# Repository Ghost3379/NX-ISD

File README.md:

# NX-ISD

## Overview
The **NX-ISD** is a custom, highly integrated wearable and embedded development board inspired by the Artemis Watch. It serves as the hardware foundation for the **ISD-Core** operating system.

> [!TIP]
> **Active Production Milestone — Hardware Revision v1.4 (Current & Recommended):**  
> Revision **v1.4** is the active, production-ready hardware milestone featuring an integrated rechargeable supercapacitor for continuous RTC timekeeping, high-speed 4-bit SDMMC MicroSD storage, a direct 40 MHz 3.3V SPI display bus (TXB0106 level shifter eliminated), tactile BOOT/RST buttons, enhanced copper heatsinking, and a cyberpunk industrial silkscreen aesthetic.  
> 📦 **Fabrication Package (Gerbers & Drill):** [`ISD-PCB/NX-ISD_v1p4/production/NX-ISD_v1p4.zip`](ISD-PCB/NX-ISD_v1p4/production/NX-ISD_v1p4.zip)  
> 📜 **Complete 5-Page Circuit Diagram:** [`docs/circuit diagrams/NX-ISD_v1p4.pdf`](docs/circuit%20diagrams/NX-ISD_v1p4.pdf)  
> 🏭 **Fabrication & Ordering Guide:** [`ISD-PCB/PRODUCTION-GUIDE.md`](ISD-PCB/PRODUCTION-GUIDE.md)

<p align="center">
  <em>NX-ISD Hardware Revision v1p4 (KiCad Raytraced 3D Renders) — Populated Top View, Bottom Silkscreen, Perspective Isometric Angle, and Bare ENIG Finish.</em>
</p>

## Naming & Structure

```text
N X - I S D
│     │
│     └─► Intelligent Sensor Device (Hardware Foundation)
│           │
│           ▼
│       ISD-Core
│           │
│           ├─► Custom Operating System (Dual-Core FreeRTOS based)
│           ├─► Built on PlatformIO / Arduino Framework
│           │
│           ├──► NX-MSF: Mathematical Sensor Fusion (Physics Models & Kalman Filters)
│           ├──► NX-AIS: Advanced Information System (Contextual Advisory Engine)
│           └──► NX-SDS: Self-Diagnostic System (Hardware Integrity & Proof-Testing)
│
└─► Prototyping Series (Continuous Development Environment)
```

* **Hardware Lineage:** Originally inspired by and iterated from the [Artemis Watch](https://circuitmess.com/products/nasa-artemis-watch) (and subsequently the [Artemis Watch 2.0](https://circuitmess.com/products/nasa-artemis-watch-2-0)) by CircuitMess, heavily expanded into a custom tactical multi-sensor wearable.
* **The "NX" Philosophy:** Inspired by Starfleet's experimental registry designation ([Memory Alpha: NX](https://memory-alpha.fandom.com/wiki/NX)), the **NX** prefix denotes an active, pioneering prototyping environment. Rather than static consumer electronics, each build is a working experimental platform. Once a revision is tagged and published, that milestone is locked in history—quirks, bugs, and all:
  * **Revision v1.4 (Current & Recommended):** Production revision with MicroSD (4-bit SDMMC), supercapacitor RTC backup, direct 40 MHz SPI display bus, and physical RST/BOOT buttons. [`ISD-PCB/NX-ISD_v1p4/`](ISD-PCB/NX-ISD_v1p4/)
  * **Revision v1.3 (Prototype Carrier):** First operational wearable prototype assembly with NAND flash and TXB0106 display shifter. [`ISD-PCB/NX-ISD_v1p3/`](ISD-PCB/NX-ISD_v1p3/)
  * **Revision v1.0 (Initial Prototype Archive):** The original, raw starting schematics, early layout, and BOM preserved for historical nostalgia, open-source transparency, and post-mortem analysis. [`ISD-PCB/NX-ISD_v1p0/`](ISD-PCB/NX-ISD_v1p0/)

## Hardware Specifications (Revision v1.4)

### Core & Storage
* **Microcontroller:** ESP32-S3-WROOM-1-N16R8 (Dual-Core Xtensa LX7 @ 240MHz, 16MB Quad-SPI Flash, 8MB Octal PSRAM)
* **High-Speed Mass Storage:** MicroSD Card Slot (`J4`, Molex 105162-0001) operating in 4-bit SDMMC bus mode via the ESP32-S3 GPIO Matrix (`SD_CLK` IO41, `SD_CMD` IO43, `SD_DAT0` IO44, `SD_DAT1` IO42, `SD_DAT2` IO1, `SD_DAT3` IO2)

### Sensors & Biometrics
* **Motion / 9-DOF IMU:** BNO085 (CEVA / Hillcrest Labs AR/VR Motion Co-Processor with dedicated 32.768 kHz crystal `Y1`)
* **Environment:** BME680 / BME690 (Bosch Sensortec Gas MOX, Barometric Pressure, Relative Humidity, Temperature)
* **Ambient Light:** OPT3001DNPR (Texas Instruments Precision Photopic Lux Sensor)
* **Biometrics / PPG:** MAX30102 (Pulse Oximetry $SpO_2$ & Heart-Rate Biosensor, isolated on 1.8V domain via PCA9306DCKR bidirectional level shifter `U9`)
* **Precision Timing & RTC:** RV-3028-C7 (Micro Crystal Switzerland, 45 nA typ.) backed by an integrated **11 mF 3.3V Seiko `CPH3225A` rechargeable supercapacitor (`C5`)** charged via internal silicon trickle charger (~6.2 days continuous autonomous timekeeping)

### Power Management & Thermal Design
* **Battery Charging:** USB-C (BQ25170 Linear LiPo Charger configured for 600mA charging into 1S 1200mAh LiPo; enhanced bottom GND thermal relief plating)
* **Fuel Gauge:** MAX17048G_T10 (ModelGauge™ cell voltage tracking, state-of-charge %, and `!ALERT` interrupt line)
* **System Rail (+3V3):** TLV62568 Synchronous Step-Down Buck Converter (1A rating, ~95% efficiency, 2.2µH power inductor)
* **Sensor Rail (+1V8):** RT9193-18GB Ultra-Low-Noise LDO (300mA rating, dedicated clean analog rail for MAX30102 core)
* **Power-Path & Switches:** High-efficiency `DMP3130L-7` P-MOSFETs for USB/Battery power-path management and NeoPixel sleep cutoff; `ZXMN3B14FTA` 30V N-MOSFETs for acoustic buzzer and display backlight control

### Peripherals & User Interaction
* **Display Interface:** [1.54" 240×240 IPS Color TFT (ST7789V2)](https://de.aliexpress.com/item/1005007654038756.html) connected via 10-pin 0.5mm dual-contact FPC connector (`J3`). Operates natively on a **direct 3.3V SPI bus at 40 MHz** (TXB0106 level shifter eliminated for rock-solid signal integrity)
* **Optical Matrix:** 16x NeoPixel 4×4 Serpentine RGB Matrix (XL-1010RGBC-WS2812B) with zero-leakage PMOS high-side power gate (`IO17` enable, `IO18` data) and local decoupling capacitors
* **Acoustic Transducer:** 16Ω Electromagnetic SMT Buzzer (`SMD-8503-3627-16Ω`) with flyback diode protection
* **Input Controls:**
  * Multi-Directional Navigation Lever-Switch (`TM-2025A` 5-way navigation: Up, Down, Left, Right, Center Push)
  * Main Tactical User Push-Button with hardware pull-up for deep-sleep wake
  * Dedicated Tactile **BOOT** (`SW2`) and **RST** (`SW1`) Micro Push-Buttons for effortless flashing and recovery

## Software & Core Systems
The board is programmed via **PlatformIO** (Arduino Framework) and is optimized to run the custom **ISD-Core** operating system. The software stack is composed of core modular subsystems:

* **[ISD-Core](ISD-Core/):** The dual-core FreeRTOS operating system handling task scheduling (Core 1 UI @ ~42Hz, Core 0 Sensors @ 50Hz/1Hz), thread-safe `SensorState` telemetry, 3D Cover Flow launcher, 360° radial dials, and smoothstep backlight transitions. See [`ISD-Core/README.md`](ISD-Core/README.md) for the software architecture and [`ISD-Core/MANUAL.md`](ISD-Core/MANUAL.md) for the complete user manual.
* **Persistent Storage Subsystem (`StorageManager`):** Manages non-volatile configuration storage, sensor logs, and system data on high-speed MicroSD storage (`4-bit SDMMC` mode on v1.4 hardware; SPI NAND on legacy v1.3 prototype). Stores a 64-byte packed binary struct (`/sys/config.bin`) with CRC-16 validation and a zero-wear save policy (writes occur only on user confirmation/exit, never while dialing).
* **Unified Host CLI & Config Engine (`tools/isd_cli.py` / `isd-cli`):** Standalone PC terminal tool providing blind navigation control, live sensor monitoring, BLE Uplink Bridge triggering, and offline `/sys/config.bin` binary inspection, verification, and JSON conversion.
* **NX-MSF (Mathematical Sensor Fusion):** The analytical physics and math engine executing 1D Kalman filter variometer tracking, Magnus-Tetens dew point calculation, barometric storm gradients, RMSSD heart rate variability, and software energy accounting.
* **NX-AIS (Advanced Information System):** The autonomous on-device contextual advisor translating raw multi-sensor telemetry into proactive health, environmental, and tactical notifications.
* **NX-SDS (Self-Diagnostic System):** The internal hardware integrity and health assurance engine providing continuous I2C bus recovery, on-demand in-situ proof-testing, and predictive battery/sensor aging analytics.

## Documentation & Manuals
* **Hardware Production & Fabrication Guide:** [`ISD-PCB/PRODUCTION-GUIDE.md`](ISD-PCB/PRODUCTION-GUIDE.md) — Complete JLCPCB ordering parameters, mechanical drawings/dimensions, stencil specs, and hand assembly workflow.
* **Fabrication Packages (Gerbers):** [`ISD-PCB/NX-ISD_v1p4/production/NX-ISD_v1p4.zip`](ISD-PCB/NX-ISD_v1p4/production/NX-ISD_v1p4.zip) — Ready-to-order RS-274X Gerbers and drill files for revision v1.4.
* **Interactive HTML BOM (Visual Assembly Tool):** [`ISD-PCB/NX-ISD_v1p4/bom/NX-ISD_v1p4_IBOM.html`](ISD-PCB/NX-ISD_v1p4/bom/NX-ISD_v1p4_IBOM.html) — Interactive visual assembly BOM highlighting components and pads.
* **User & Navigation Manual:** [`ISD-Core/MANUAL.md`](ISD-Core/MANUAL.md) — Comprehensive guide covering physical controls, screen layouts, the 6 core application decks, 360° radial dials, and storage persistence.
* **Architecture & Hardware Guide:** [`ISD-Core/README.md`](ISD-Core/README.md) — Technical operating system internals, pin maps, and PlatformIO build instructions.
* **Hardware & PCB Specifications:** [`ISD-PCB/README.md`](ISD-PCB/README.md) — Hardware schematics, power budgets, layer stackup, and BOM.
* **Features & Math Modeling Roadmap:** [`FEATURE_LIST.md`](FEATURE_LIST.md) — Technical specifications, mathematical formulas, and implementation roadmap.
* **Software Roadmap & TODOs:** [`ISD-Core/SW-TODO.md`](ISD-Core/SW-TODO.md) — Core application deck progress and feature checklist.

## AI Collaboration & Transparency Disclaimer
In the spirit of full open-source transparency:
* **AI Assistance:** Generative AI pair-programming tools were used to assist with documentation drafting, software architecture refinement, mathematical formula translations, and repository organization.
* **Engineering & Ownership:** All hardware schematics, PCB routing, component selection, electrical calculations, physical assembly, and system verification remain 100% human-engineered, tested, and maintained by the author ([@Ghost3379](https://github.com/Ghost3379)).

## License
The software/firmware in the [ISD-Core] directory is licensed under the GNU General Public License v3.0 (GPLv3).

The hardware design files in the [ISD-PCB] directory are licensed under the CERN Open Hardware Licence Version 2 - Strongly Reciprocal (CERN-OHL-S).

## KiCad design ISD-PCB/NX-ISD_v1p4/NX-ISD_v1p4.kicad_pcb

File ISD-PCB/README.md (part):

# NX-ISD Hardware Specification (Revision v1p4 - Current & Recommended)

This directory contains the schematic design, PCB layout, fabrication outputs, and Bill of Materials (BOM) for the **NX-ISD** (Intelligent Sensor Device) wearable carrier board.

<p align="center">
  <em>NX-ISD Hardware Revision v1p4 (KiCad Raytraced 3D Renders) — Populated Top View, Bottom Silkscreen, Perspective Isometric Angle, and Bare ENIG Finish with "PUT THAT BACK!" Silkscreen Easter Egg</em>
</p>

> [!TIP]
> **Production & Ordering Guide (v1.4):** For complete mechanical drawings, JLCPCB ordering parameters, SMD stencil specs, and hand assembly tips, see the **[Production Guide](PRODUCTION-GUIDE.md)**.  
> 📦 **Latest v1.4 Fabrication Package:** [`NX-ISD_v1p4/production/NX-ISD_v1p4.zip`](NX-ISD_v1p4/production/NX-ISD_v1p4.zip) (Ready for JLCPCB / PCBWay).  
> 📜 **Latest v1.4 Circuit Diagram (5 Sheets):** [`../docs/circuit diagrams/NX-ISD_v1p4.pdf`](../docs/circuit%20diagrams/NX-ISD_v1p4.pdf).

---

## 1. Board Specifications & Physical Dimensions

| Parameter | Specification | Notes |
| :--- | :--- | :--- |
| **Dimensions** | **77.00 mm × 48.60 mm** | Measured outer bounding box on `Edge.Cuts` |
| **Board Thickness** | **1.2 mm** | Standard FR-4 rigid substrate (optimal wrist comfort & rigidity) |
| **Layer Count** | **4 Layers** | Optimized signal integrity, unbroken GND plane, and dedicated power pours |
| **Copper Weight** | 1 oz Outer (35 µm), 1 oz Inner | Standard manufacturing yield with thermal relief |
| **Surface Finish** | ENIG (Electroless Nickel Immersion Gold) | Mandatory for fine-pitch QFN/WSON sensors and 0402 passives |
| **Strap Mounts** | Dual integrated strap slots | Accommodates standard 20 mm – 28 mm watch straps |
| **Antenna Clearance** | Dedicated bottom keep-out zone | `RF-AREA KEEP FREE` silkscreen below ESP32-S3 PCB antenna |
| **Primary Connector** | 16-Pin Mid-Mount USB Type-C | USB 2.0 Full Speed + 5V 600mA charging |
| **Battery Header** | JST PH 2.0mm 2-Pin (`J2`) | Polarized 1S LiPo (1200 mAh form factor) |
| **Mass Storage** | Push-Pull MicroSD Socket (`J4`) | High-speed 4-bit SDMMC bus interface |

### 4-Layer PCB Stackup

```text
┌────────────────────────────────────────────────────────────────────────┐
│ Layer 1: Top (F.Cu)       High-density signal routing, IC pads, GND    │
├────────────────────────────────────────────────────────────────────────┤
│ Layer 2: Inner 1 (In1.Cu) Solid uninterrupted Ground Plane (GND)       │
├────────────────────────────────────────────────────────────────────────┤
│ Layer 3: Inner 2 (In2.Cu) Power Planes (+3V3, VBAT, +1V8, VN)          │
├────────────────────────────────────────────────────────────────────────┤
│ Layer 4: Bottom (B.Cu)    Secondary routing, thermal pads, silkscreen  │
└────────────────────────────────────────────────────────────────────────┘
```

---

## 2. Power Architecture & Voltage Domains (v1.4)

```text
               ┌───────────────────────┐
  USB-C (5V) ─►│ BQ25170 Charger (U3)  ├──► VBAT (3.7V - 4.2V, 1S LiPo via J2)
               │ (600mA, 10k NTC TH1)  │         │
               └───────────────────────┘         ├─► MAX17048 Fuel Gauge (U6)
                                                 │
  ┌──────────────────────────────────────────────┘
  │
  ├──► TLV62568 Buck Converter (U4) ──► +3V3 (System Rail, ~95% Efficiency)
  │    (2.2µH L1, 10µF filtering)         │
  │                                       ├─► ESP32-S3 Microcontroller (U2)
  │                                       ├─► BNO085 9-DOF IMU (U11)
  │                                       ├─► BME690 Environmental (U7)
  │                                       ├─► OPT3001 Ambient Light (U10)
  │                                       ├─► RV-3028-C7 RTC (U12)
  │                                       ├─► MicroSD Card Slot (J4)
  │                                       ├─► ST7789 IPS Display Logic & Backlight (J3 / Q4)
  │                                       └─► Buzzer LS1 (via Q3)
  │
  ├──► RT9193-18GB LDO (U5) ──────────► +1V8 (Ultra-Low-Noise Sensor Rail)
  │    (Ultra-Low Noise, 300mA)           ├─► MAX30102 PPG / Biometrics (U8)
  │                                       └─► PCA9306 I2C Level Shifter (U9, Port 1)
  │
  ├──► DMP3130L-7 PMOS Gate (Q1) ──────► VN   (Switched VBAT Rail, 3.0V - 4.2V)
  │    (Driven by IO17 via BC847W)        └─► 16x NeoPixel Matrix (G1..G16)
  │                                           [Guarantees 0µA sleep draw]
  │
  └──► RV-3028-C7 Internal Charger ───► VBACKUP (Autonomous Supercapacitor Rail)
       (Switch + Schottky + 3k Ladder)    └─► 11mF 3.3V Seiko CPH3225A (C5)
                                              [~6.2 Days RTC timekeeping backup]
```

### Voltage Rail Details

| Rail | Nominal Voltage | Regulator / Source | Max Current | Consumers |
| :--- | :--- | :--- | :--- | :--- |
| **`VBUS`** | 5.0 V (4.75–5.25V) | USB Type-C Receptacle (`J1`) | 1.5 A | BQ25170 Charger, USB detect divider, USBLC6 ESD |
| **`VBAT`** | 3.7 V (3.0–4.2V) | 1S LiPo via JST PH (`J2`) | 2.0 A peak | Buck converter, LDO, Fuel Gauge, VN PMOS switch, Power-Path PMOS (`Q2`) |
| **`+3V3`** | 3.3 V (±1.5%) | TLV62568DBVR Synchronous Buck (`U4`)| 1.0 A | ESP32-S3, BNO085, BME690, OPT3001, RV-3028, MicroSD, ST7789 Display, Buzzer |
| **`+1V8`** | 1.8 V (±2.0%) | RT9193-18GB Low-Noise LDO (`U5`) | 300 mA | MAX30102 logic core, PCA9306 level shifter low-side |
| **`VN`** | Switched `VBAT` | DMP3130L-7 High-Side PMOS (`Q1`) | 1.0 A | 16x XL-1010RGBC NeoPixels (0µA cutoff when unpowered) |
| **`VBACKUP`**| 3.3 V max (1.1–3.05V)| RV-3028-C7 Internal Trickle Charger| 1.0 mA chg | Pin 6 of RV-3028-C7 backed by $11\text{ mF}$ CPH3225A Supercap (`C5`) |

---

## 3. Power Consumption Budget & Battery Calculation

Comprehensive current consumption analysis across operating states, accounting for conversion efficiencies and real-world loads:

### 1. Subsystem Current Breakdown

#### A. 16× NeoPixel RGB Matrix (`G1`–`G16`, on Switched `VN` / `VBAT`)
* **Driver Constant-Current Sink:** $5.0\,\text{mA}$ per color channel (R, G, B).
* **Per LED at 100% White:** $(3 \times 5.0\,\text{mA}) + 0.35\,\text{mA}$ (internal logic) $\approx \mathbf{15.35\,\text{mA}}$.
* **100% White Matrix Stress Test (16 LEDs):** $16 \times 15.35\,\text{mA} \approx \mathbf{245.6\,\text{mA}}$ (drawn directly from `VBAT` through PMOS `Q2`).
* **Dynamic Cyberpunk Animations (`CYBER RADAR`, `NEON TRACER`, etc.):** 2 to 5 active LEDs at 30–60% intensity $\approx \mathbf{15\text{ to }35\,\text{mA}}$ average.
* **Standby / Off State (`PWR_NPM` = LOW):** High-side PMOS `Q2` is gated off by pull-up $\implies \mathbf{0.00\,\mu\text{A}}$ (completely eliminates NeoPixel quiescent leakage).

#### B. ESP32-S3 Dual-Core Microcontroller (`U13`, on `+3V3`)
* **Active Wi-Fi TX (Max power + Dual-Core processing):** $\approx 240\text{ to }350\,\text{mA}$ (transient peaks up to $\approx 450\,\text{mA}$).
* **Active BLE Connected / Advertising:** $\approx 35\text{ to }55\,\text{mA}$.
* **Normal Dual-Core Processing (No RF, 240 MHz):** $\approx 40\text{ to }65\,\text{mA}$.
* **Frequency-Scaled Run (80 MHz / 160 MHz):** $\approx 20\text{ to }35\,\text{mA}$.
* **FreeRTOS Light-Sleep (Between 50Hz/1Hz sensor ticks):** $\approx 1.5\text{ to }3.0\,\text{mA}$.
* **Deep-Sleep (ULP / RTC wake only):** $\approx 15\text{ to }25\,\mu\text{A}$.

#### C. ST7789 IPS Display (`J2`, on `+3V3` & `+2V8`)
* **Backlight LEDs (via `+3V3` switched by N-MOSFET `Q4`):**
  * 100% Brightness: $\approx 35\text{ to }45\,\text{mA}$.
  * 40% Indoor Brightness: $\approx 15\text{ to }20\,\text{mA}$.
* **Display Controller Logic (via `+2V8` LDO `U4`):** $\approx 5\text{ to }10\,\text{mA}$.
* **Display Sleep Mode (`SLPIN` command):** $< 20\,\mu\text{A}$.
* **Total Display Active:** $\approx 20\text{ to }55\,\text{mA}$.

#### D. Sensors, Audio & Storage Peripherals
* **MAX30102 Biometrics (`U8`, on `+1V8` LDO `U1`):**
  * Time-averaged optical pulse current (Red + IR LEDs @ 50–100 Hz): $\approx 10\text{ to }18\,\text{mA}$ (peaks of $50\,\text{mA}$ during $400\,\mu\text{s}$ pulses).
  * Standby / Shutdown: $< 1\,\mu\text{A}$.
* **BNO085 9-DOF IMU (`U11`, on `+3V3`):**
  * Active 9-axis sensor fusion (internal ARM Cortex-M0+ running at 100 Hz): $\approx 15\text{ to }18\,\text{mA}$.
  * Low-power tap / step-detector only: $\approx 0.8\text{ to }1.5\,\text{mA}$.
* **BME690 Environmental (`U7`, on `+3V3`):**
  * Base climate sampling (T/P/H): $< 1\,\text{mA}$.
  * MOX Gas Heater Pulse (heats to $320^\circ\text{C}$ for $\approx 30\,\text{ms}$): $\mathbf{+12\text{ to }14\,\text{mA}}$ transient burst.
* **B1 Electromagnetic Buzzer (`B1`, on `+3V3` via `Q3`):**
  * $16\,\Omega$ coil impedance at $3.3\,\text{V}$: Peak current $\approx 206\,\text{mA}$.
  * 50% PWM Duty Cycle acoustic tone: $\approx \mathbf{80\text{ to }100\,\text{mA}}$ average (only when sounding alert/alarm).
* **ZDSD02GLGEAG SPI NAND Flash (`U14`, on `+3V3`):**
  * Standby: $\approx 10\,\mu\text{A}$.
  * High-speed SPI Read/Write bursts: $\approx 15\text{ to }25\,\text{mA}$.
* **OPT3001 Ambient Light (`U10`, on `+3V3`):** $\approx 2\text{ to }4\,\mu\text{A}$ (quiescent).
* **RV-3028-C7 RTC (`U12`, on `+3V3`):** $\approx 45\,\text{nA}$ (running continuously).
* **LDO Quiescent Currents (`U1`, `U4`):** $\approx 90\,\mu\text{A}$ each.

---

### 2. Supply Rail Power Budget & Buck Efficiency

#### `+3V3` System Rail (TLV62568 Synchronous Buck `U3`):
* **Normal Operation (Display on, sensors active, Wi-Fi off):** $\approx 80\text{ to }130\,\text{mA}$.
* **Full Load (Wi-Fi TX active, display 100%, all sensors active, BME690 heater):** $\approx \mathbf{320\text{ to }460\,\text{mA}}$.
* **Absolute Worst-Case Transient (+ Buzzer beeping):** $\approx 550\text{ to }640\,\text{mA}$.
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
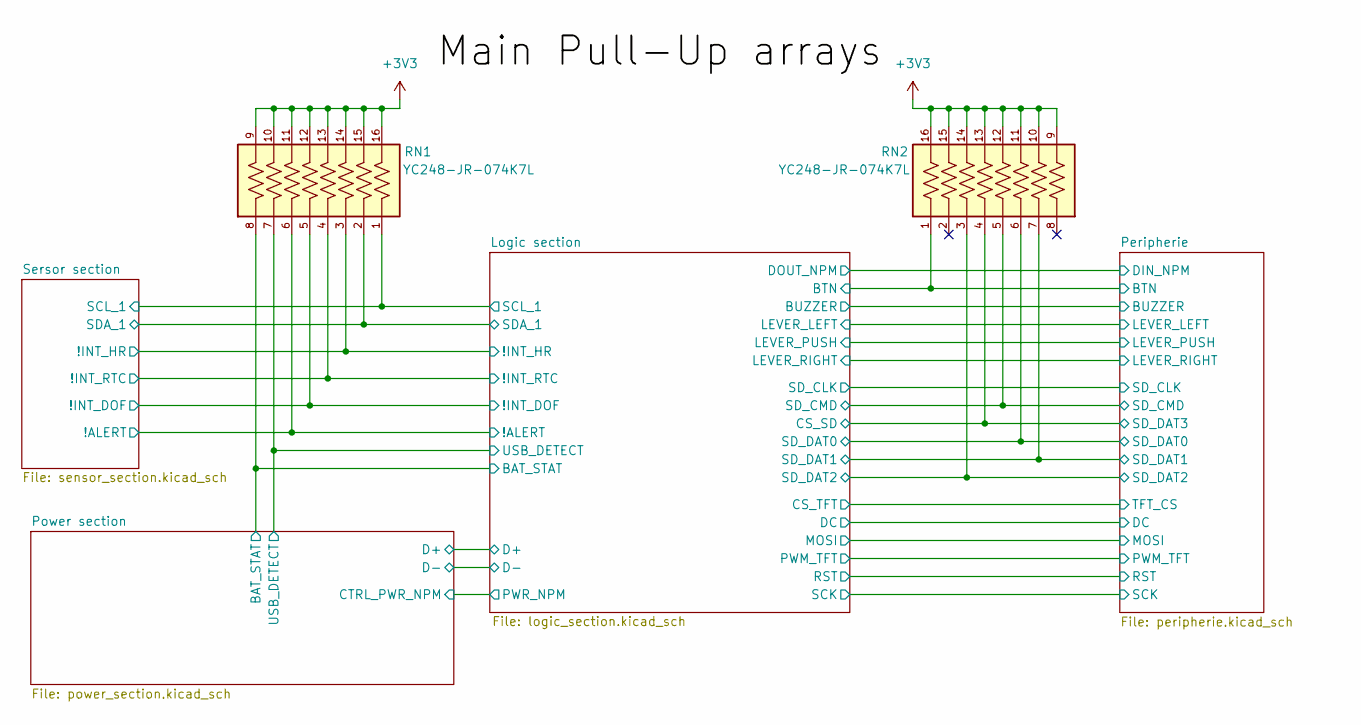
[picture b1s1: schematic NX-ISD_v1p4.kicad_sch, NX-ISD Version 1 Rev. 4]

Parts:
RN1, RN2: YC248-JR-074K7L; RESCAXS50P400X160X55-16N; PARTREV V1.0

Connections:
+3V3: RN1.9, RN1.10, RN1.11, RN1.12, RN1.13, RN1.14, RN1.15, RN1.16, RN2.9, RN2.10, RN2.11, RN2.12, RN2.13, RN2.14, RN2.15, RN2.16; also elsewhere on the board
/Logic section/!ALERT: RN1.6; also elsewhere on the board
/Logic section/!INT_DOF: RN1.5; also elsewhere on the board
/Logic section/!INT_HR: RN1.3; also elsewhere on the board
/Logic section/!INT_RTC: RN1.4; also elsewhere on the board
/Logic section/BAT_STAT: RN1.8; also elsewhere on the board
/Logic section/BTN: RN2.1; also elsewhere on the board
/Logic section/CS_SD: RN2.4; also elsewhere on the board
/Logic section/SCL_1: RN1.1; also elsewhere on the board
/Logic section/SDA_1: RN1.2; also elsewhere on the board
/Logic section/SD_CMD: RN2.5; also elsewhere on the board
/Logic section/SD_DAT0: RN2.6; also elsewhere on the board
/Logic section/SD_DAT1: RN2.7; also elsewhere on the board
/Logic section/SD_DAT2: RN2.3; also elsewhere on the board
/Logic section/USB_DETECT: RN1.7; also elsewhere on the board

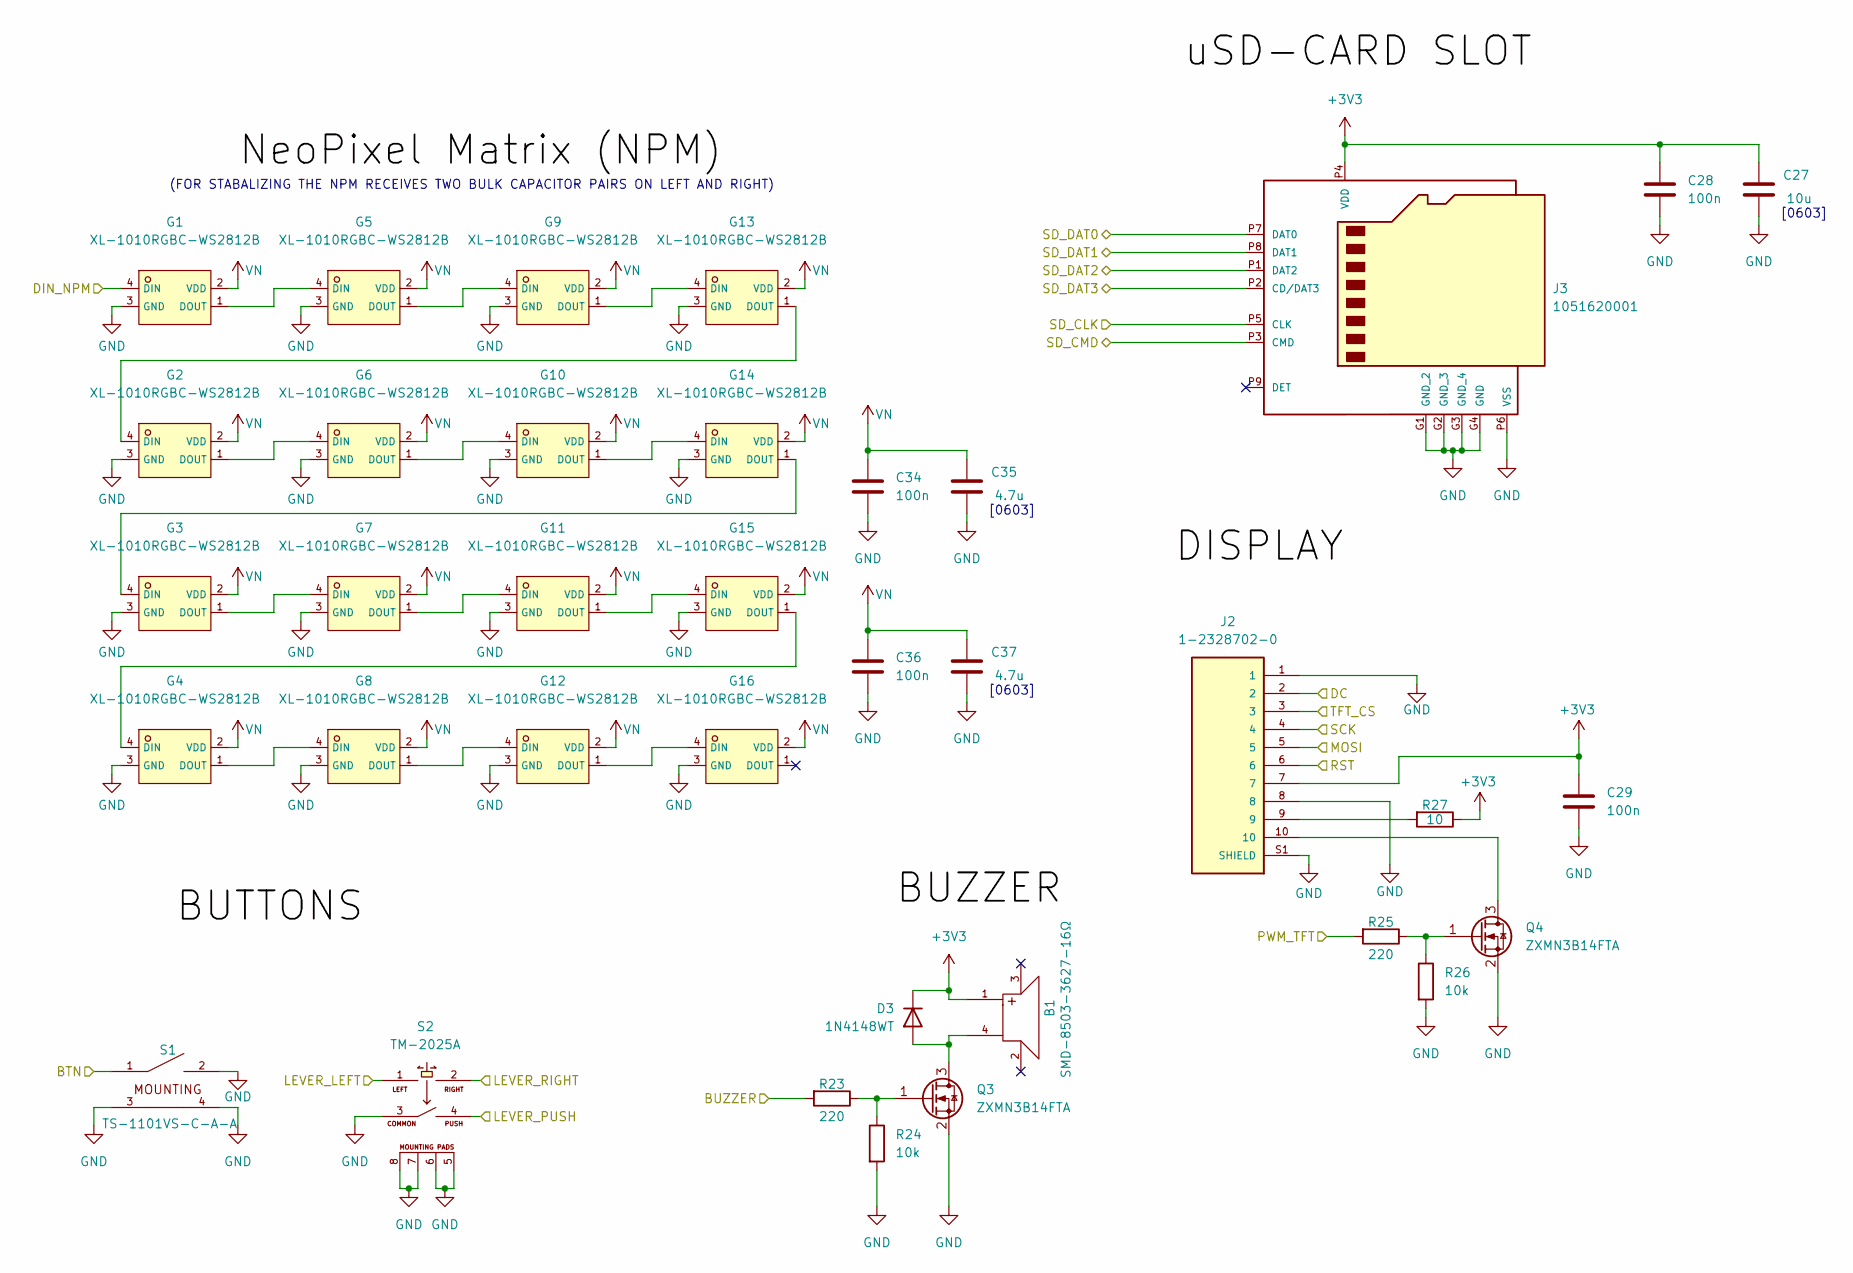
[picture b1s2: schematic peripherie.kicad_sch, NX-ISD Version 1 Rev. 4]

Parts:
B1: SMD-8503-3627-16Ω; BUZ-SMD_4P-L8.5-W8.5-BR-1; LCSC C2685545
C27: 10u; C_0603_1608Metric
C28, C29, C34, C36: 100n; C_0402_1005Metric
C35, C37: 4.7u; C_0603_1608Metric
D3: 1N4148WT; D_SOD-523
G1, G2, G3, G4, G5, G6, G7, G8, G9, G10, G11, G12, G13, G14, G15, G16: XL-1010RGBC-WS2812B; LED-SMD_4P-L1.0-W1.0-TL_XL-1010RGBC-WS2812B; LCSC C5349953
J2: 1-2328702-0; TE_1-2328702-0; PARTREV 5
J3: 1051620001; 105162-0001_MOL; MANUFACTURER_PART_NUMBER 1051620001
Q3, Q4: ZXMN3B14FTA; SOT-23
R23, R25: 220; R_0402_1005Metric
R24, R26: 10k; R_0402_1005Metric
R27: 10; R_0402_1005Metric
S1: TS-1101VS-C-A-A; KEY-SMD_TS-1101VS-C-A-A
S2: TM-2025A; SW-SMD_TM-2025A; LCSC C318949

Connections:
+3V3: B1.1, C27.1, C28.1, C29.1, D3.1 (K), J2.7, J3.P4 (VDD), R27.1; also elsewhere on the board
/Logic section/BTN: S1.1; also elsewhere on the board
/Logic section/CS_SD: J3.P2 (CD/DAT3); also elsewhere on the board
/Logic section/CS_TFT: J2.3; also elsewhere on the board
/Logic section/DC: J2.2; also elsewhere on the board
/Logic section/DOUT_NPM: G1.4 (DIN); also elsewhere on the board
/Logic section/LEVER_LEFT: S2.1; also elsewhere on the board
/Logic section/LEVER_PUSH: S2.4; also elsewhere on the board
/Logic section/LEVER_RIGHT: S2.2; also elsewhere on the board
/Logic section/MOSI: J2.5; also elsewhere on the board
/Logic section/PWM_TFT: R25.2; also elsewhere on the board
/Logic section/RST: J2.6; also elsewhere on the board
/Logic section/SCK: J2.4; also elsewhere on the board
/Logic section/SD_CLK: J3.P5 (CLK); also elsewhere on the board
/Logic section/SD_CMD: J3.P3 (CMD); also elsewhere on the board
/Logic section/SD_DAT0: J3.P7 (DAT0); also elsewhere on the board
/Logic section/SD_DAT1: J3.P8 (DAT1); also elsewhere on the board
/Logic section/SD_DAT2: J3.P1 (DAT2); also elsewhere on the board
/Peripherie/BUZZER: R23.2; also elsewhere on the board
GND: C27.2, C28.2, C29.2, C34.2, C35.2, C36.2, C37.2, G1.3 (GND), G2.3 (GND), G3.3 (GND), G4.3 (GND), G5.3 (GND), G6.3 (GND), G7.3 (GND), G8.3 (GND), G9.3 (GND), G10.3 (GND), G11.3 (GND), G12.3 (GND), G13.3 (GND), G14.3 (GND), G15.3 (GND), G16.3 (GND), J2.1, J2.8, J2.S1 (SHIELD), J2.S2 (SHIELD), J3.G1 (GND_2), J3.G2 (GND_3), J3.G3 (GND_4), J3.G4 (GND), J3.P6 (VSS), Q3.2 (S), Q4.2 (S), R24.2, R26.2, S1.2, S1.3, S1.4, S2.3, S2.5, S2.6, S2.7, S2.8; also elsewhere on the board
unnamed: B1.4, D3.2 (A), Q3.3 (D)
unnamed: G1.1 (DOUT), G5.4 (DIN)
unnamed: G2.1 (DOUT), G6.4 (DIN)
unnamed: G3.1 (DOUT), G7.4 (DIN)
unnamed: G4.1 (DOUT), G8.4 (DIN)
unnamed: G5.1 (DOUT), G9.4 (DIN)
unnamed: G6.1 (DOUT), G10.4 (DIN)
unnamed: G10.1 (DOUT), G14.4 (DIN)
unnamed: G7.1 (DOUT), G11.4 (DIN)
unnamed: G11.1 (DOUT), G15.4 (DIN)
unnamed: G8.1 (DOUT), G12.4 (DIN)
unnamed: G12.1 (DOUT), G16.4 (DIN)
unnamed: G9.1 (DOUT), G13.4 (DIN)
unnamed: G2.4 (DIN), G13.1 (DOUT)
unnamed: G3.4 (DIN), G14.1 (DOUT)
unnamed: G4.4 (DIN), G15.1 (DOUT)
unnamed: J2.9, R27.2
unnamed: Q3.1 (G), R23.1, R24.1
unnamed: J2.10, Q4.3 (D)
unnamed: Q4.1 (G), R25.1, R26.1
VN: C34.1, C35.1, C36.1, C37.1, G1.2 (VDD), G2.2 (VDD), G3.2 (VDD), G4.2 (VDD), G5.2 (VDD), G6.2 (VDD), G7.2 (VDD), G8.2 (VDD), G9.2 (VDD), G10.2 (VDD), G11.2 (VDD), G12.2 (VDD), G13.2 (VDD), G14.2 (VDD), G15.2 (VDD), G16.2 (VDD); also elsewhere on the board

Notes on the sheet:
[0603]
(FOR STABALIZING THE NPM RECEIVES TWO BULK CAPACITOR PAIRS ON LEFT AND RIGHT)

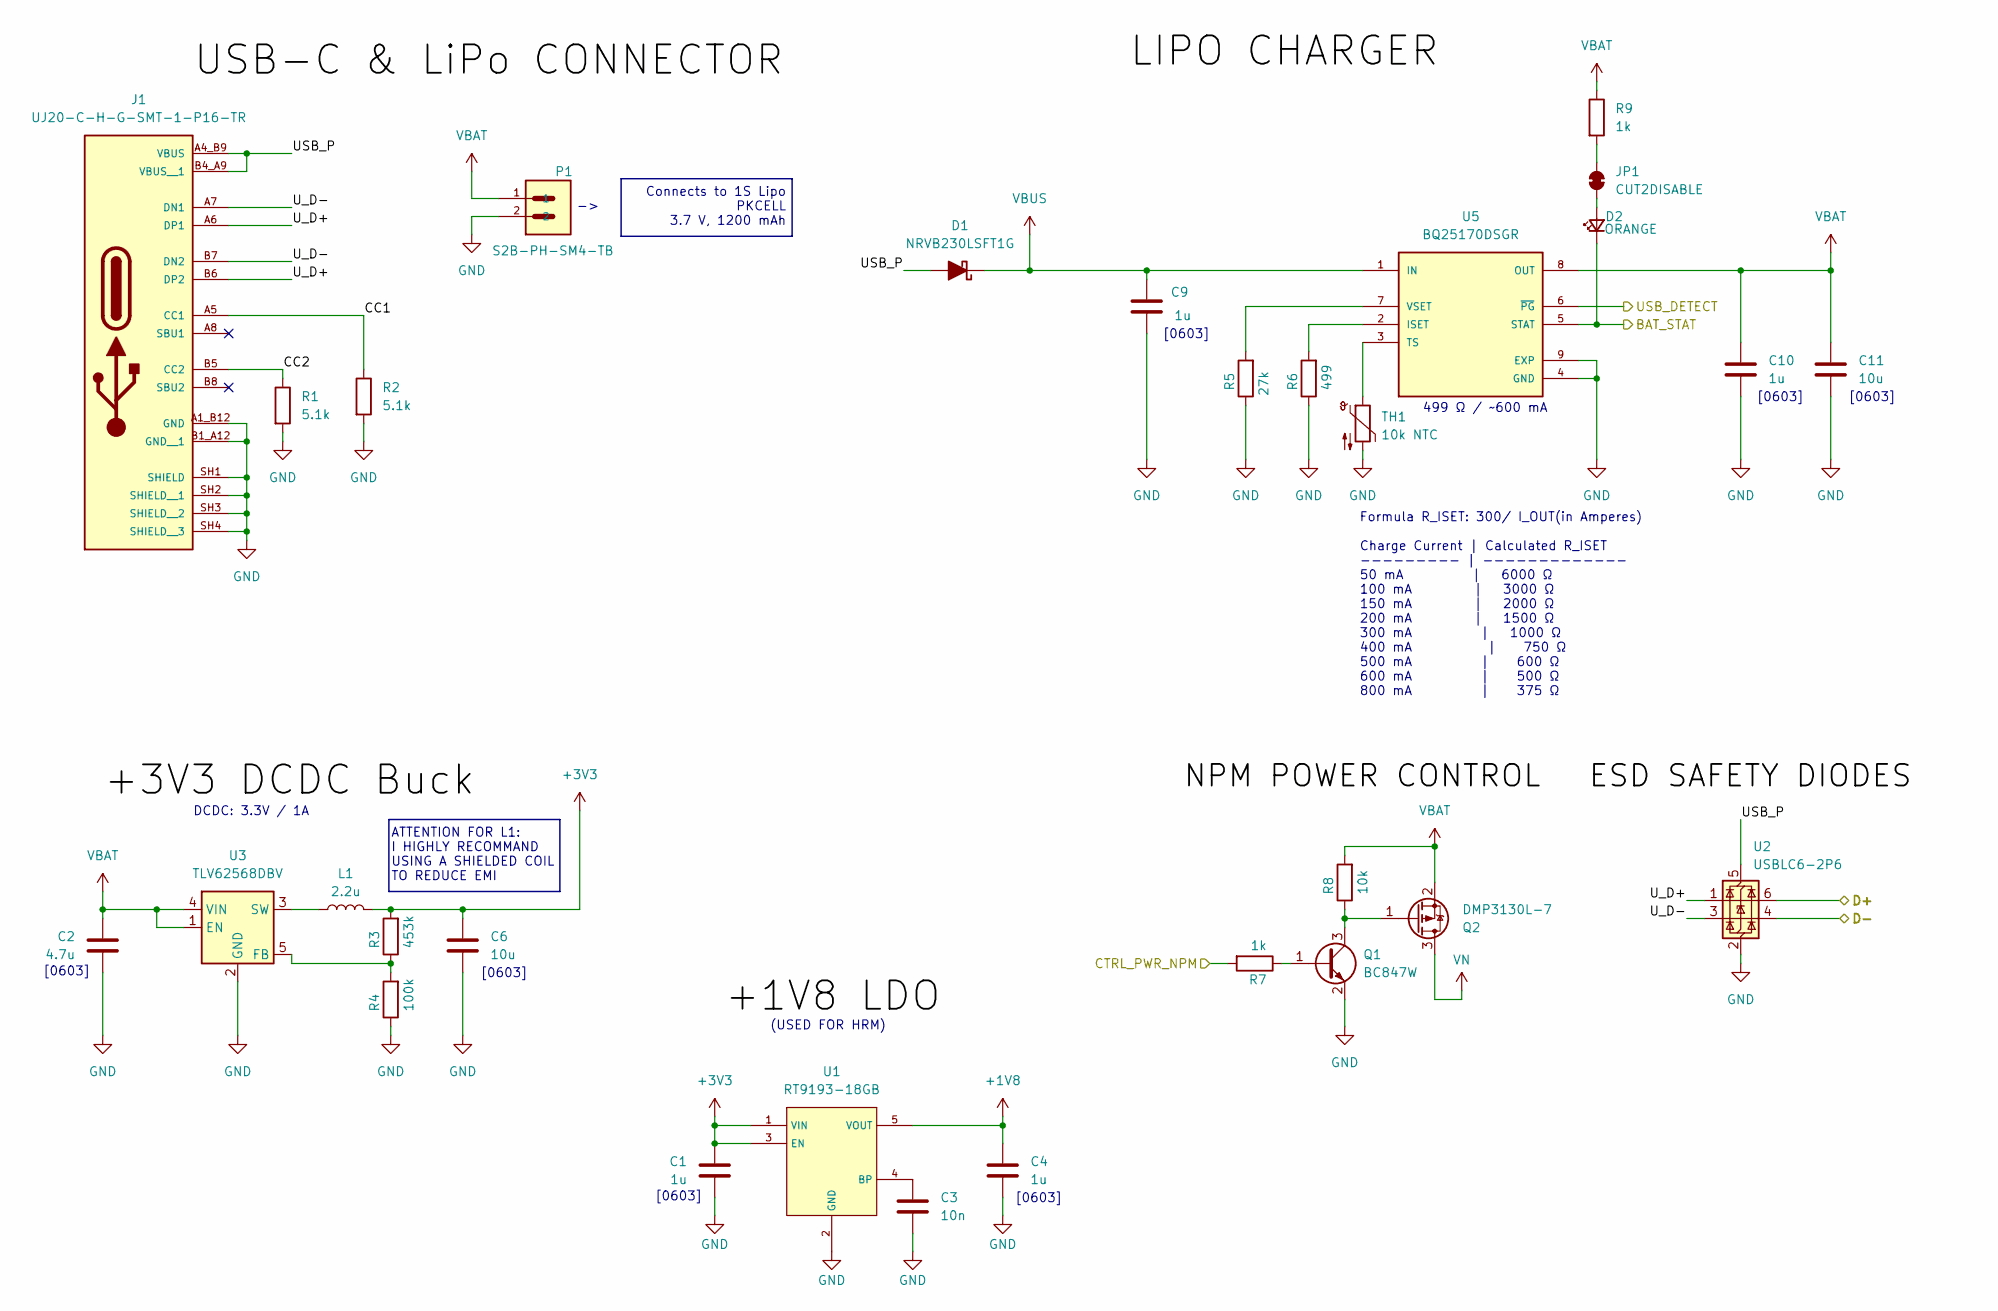
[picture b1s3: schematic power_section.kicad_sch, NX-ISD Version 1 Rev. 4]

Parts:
C1, C4, C9, C10: 1u; C_0603_1608Metric
C2: 4.7u; C_0603_1608Metric
C3: 10n; C_0402_1005Metric
C6, C11: 10u; C_0603_1608Metric
D1: NRVB230LSFT1G; D_SOD-123
D2: ORANGE; LED_0603_1608Metric
J1: UJ20-C-H-G-SMT-1-P16-TR; SAMESKY_UJ20-C-H-G-SMT-1-P16-TR; PARTREV 1.0
JP1: CUT2DISABLE; SolderJumper-2_P1.3mm_Bridged_Pad1.0x1.5mm
L1: 2.2u; L_1008_2520Metric; Manufacturer part number SRN2510BTA-2R2M
P1: S2B-PH-SM4-TB; JST_S2B-PH-SM4-TB
Q1: BC847W; SOT-323_SC-70
Q2: DMP3130L-7; SOT-23
R1, R2: 5.1k; R_0402_1005Metric
R3: 453k; R_0402_1005Metric
R4: 100k; R_0402_1005Metric
R5: 27k; R_0402_1005Metric
R6: 499; R_0402_1005Metric
R7, R9: 1k; R_0402_1005Metric
R8: 10k; R_0402_1005Metric
TH1: 10k NTC; R_0402_1005Metric; Manufacturer part number NCU15XH103D60RC
U1: RT9193-18GB; SOT23-5; LCSC C27416
U2: USBLC6-2P6; SOT-666
U3: TLV62568DBV; SOT-23-5
U5: BQ25170DSGR; SON50P200X200X80-9N; PARTREV A

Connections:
+1V8: C4.1, U1.5 (VOUT); also elsewhere on the board
+3V3: C1.1, C6.1, L1.2, R3.2, U1.1 (VIN), U1.3 (EN); also elsewhere on the board
/Logic section/BAT_STAT: D2.1 (K), U5.5 (STAT); also elsewhere on the board
/Logic section/D+: U2.6 (I/O1); also elsewhere on the board
/Logic section/D-: U2.4 (I/O2); also elsewhere on the board
/Logic section/PWR_NPM: R7.2; also elsewhere on the board
/Logic section/USB_DETECT: U5.6 (~PG); also elsewhere on the board
/Power section/CC1: J1.A5 (CC1), R2.1
/Power section/CC2: J1.B5 (CC2), R1.1
/Power section/USB_P: D1.2 (A), J1.A4_B9 (VBUS), J1.B4_A9 (VBUS__1), U2.5 (VBUS)
/Power section/U_D+: J1.A6 (DP1), J1.B6 (DP2), U2.1 (I/O1)
/Power section/U_D-: J1.A7 (DN1), J1.B7 (DN2), U2.3 (I/O2)
GND: C1.2, C2.2, C3.2, C4.2, C6.2, C9.2, C10.2, C11.2, J1.A1_B12 (GND), J1.B1_A12 (GND__1), J1.SH1 (SHIELD), J1.SH2 (SHIELD__1), J1.SH3 (SHIELD__2), J1.SH4 (SHIELD__3), P1.2, Q1.2 (E), R1.2, R2.2, R4.1, R5.1, R6.1, TH1.2, U1.2 (GND), U2.2 (GND), U3.2 (GND), U5.4 (GND), U5.9 (EXP); also elsewhere on the board
unnamed: D2.2 (A), JP1.2 (B)
unnamed: JP1.1 (A), R9.2
unnamed: Q1.1 (B), R7.1
unnamed: Q1.3 (C), Q2.1 (G), R8.1
unnamed: C3.1, U1.4 (BP)
unnamed: R3.1, R4.2, U3.5 (FB)
unnamed: L1.1, U3.3 (SW)
unnamed: R6.2, U5.2 (ISET)
unnamed: TH1.1, U5.3 (TS)
unnamed: R5.2, U5.7 (VSET)
VBAT: C2.1, C10.1, C11.1, P1.1, Q2.2 (S), R8.2, R9.1, U3.1 (EN), U3.4 (VIN), U5.8 (OUT); also elsewhere on the board
VBUS: C9.1, D1.1 (K), U5.1 (IN)
VN: Q2.3 (D); also elsewhere on the board

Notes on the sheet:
Connects to 1S Lipo -> PKCELL 3.7 V, 1200 mAh
[0603]
(USED FOR HRM)
ATTENTION FOR L1: I HIGHLY RECOMMAND USING A SHIELDED COIL TO REDUCE EMI
499 Ω / ~600 mA
DCDC: 3.3V / 1A
Formula R_ISET: 300/ I_OUT(in Amperes) Charge Current | Calculated R_ISET --------- | ------------- 50 mA | 6000 Ω 100 mA | 3000 Ω 150 mA | 2000 Ω 200 mA | 1500 Ω 300 mA | 1000 Ω 400 mA | 750 Ω 500 mA | 600 Ω 600 mA | 500 Ω 800 mA | 375 Ω

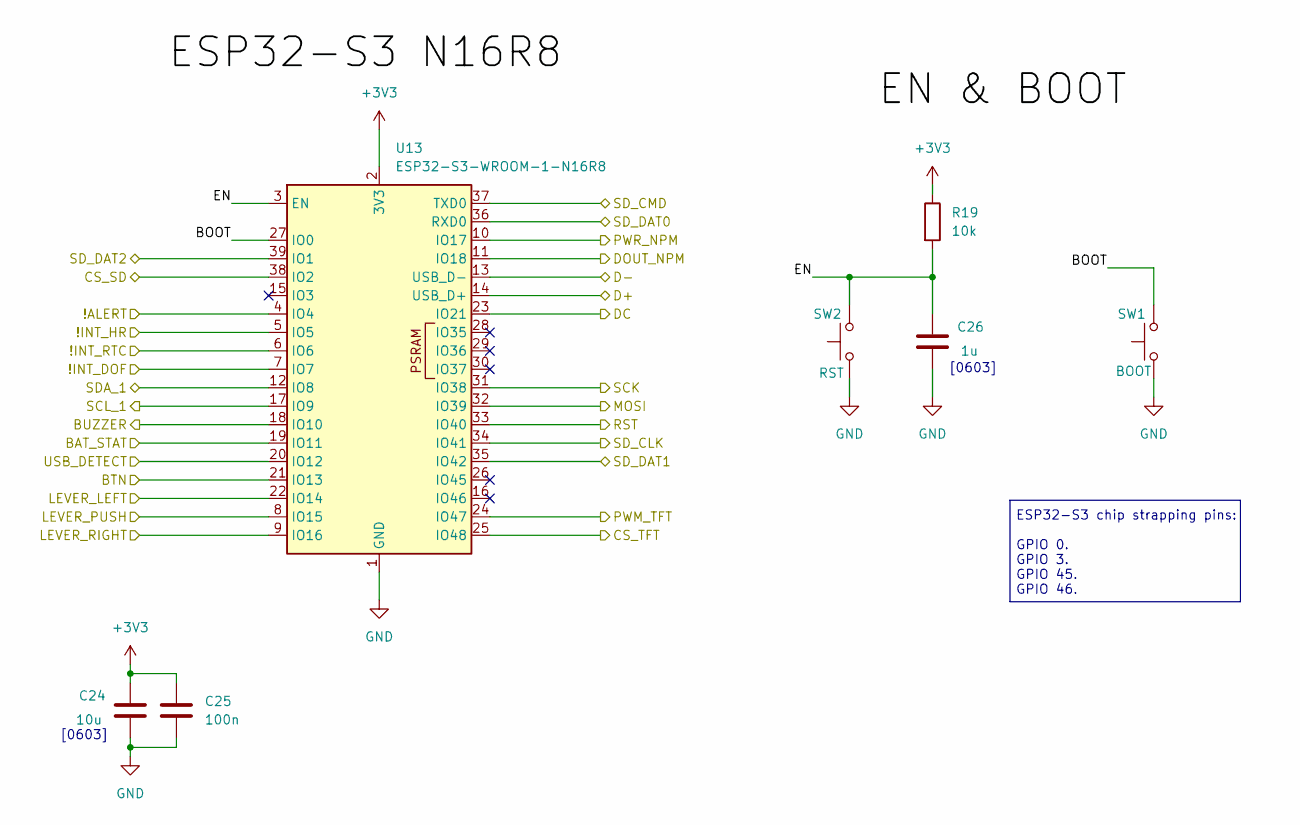
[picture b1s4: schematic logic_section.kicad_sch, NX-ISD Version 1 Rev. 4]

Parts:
C24: 10u; C_0603_1608Metric
C25: 100n; C_0402_1005Metric
C26: 1u; C_0603_1608Metric
R19: 10k; R_0402_1005Metric
SW1: BOOT; SW_SPST_PTS810
SW2: RST; SW_SPST_PTS810
U13: ESP32-S3-WROOM-1-N16R8; ESP32-S3-WROOM-1; MPN ESP32-S3-WROOM-1-N16R8

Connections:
+3V3: C24.1, C25.1, R19.1, U13.2 (3V3); also elsewhere on the board
/Logic section/!ALERT: U13.4 (IO4); also elsewhere on the board
/Logic section/!INT_DOF: U13.7 (IO7); also elsewhere on the board
/Logic section/!INT_HR: U13.5 (IO5); also elsewhere on the board
/Logic section/!INT_RTC: U13.6 (IO6); also elsewhere on the board
/Logic section/BAT_STAT: U13.19 (IO11); also elsewhere on the board
/Logic section/BOOT: SW1.2, U13.27 (IO0)
/Logic section/BTN: U13.21 (IO13); also elsewhere on the board
/Logic section/CS_SD: U13.38 (IO2); also elsewhere on the board
/Logic section/CS_TFT: U13.25 (IO48); also elsewhere on the board
/Logic section/D+: U13.14 (USB_D+); also elsewhere on the board
/Logic section/D-: U13.13 (USB_D-); also elsewhere on the board
/Logic section/DC: U13.23 (IO21); also elsewhere on the board
/Logic section/DOUT_NPM: U13.11 (IO18); also elsewhere on the board
/Logic section/EN: C26.1, R19.2, SW2.2, U13.3 (EN)
/Logic section/LEVER_LEFT: U13.22 (IO14); also elsewhere on the board
/Logic section/LEVER_PUSH: U13.8 (IO15); also elsewhere on the board
/Logic section/LEVER_RIGHT: U13.9 (IO16); also elsewhere on the board
/Logic section/MOSI: U13.32 (IO39); also elsewhere on the board
/Logic section/PWM_TFT: U13.24 (IO47); also elsewhere on the board
/Logic section/PWR_NPM: U13.10 (IO17); also elsewhere on the board
/Logic section/RST: U13.33 (IO40); also elsewhere on the board
/Logic section/SCK: U13.31 (IO38); also elsewhere on the board
/Logic section/SCL_1: U13.17 (IO9); also elsewhere on the board
/Logic section/SDA_1: U13.12 (IO8); also elsewhere on the board
/Logic section/SD_CLK: U13.34 (IO41); also elsewhere on the board
/Logic section/SD_CMD: U13.37 (TXD0); also elsewhere on the board
/Logic section/SD_DAT0: U13.36 (RXD0); also elsewhere on the board
/Logic section/SD_DAT1: U13.35 (IO42); also elsewhere on the board
/Logic section/SD_DAT2: U13.39 (IO1); also elsewhere on the board
/Logic section/USB_DETECT: U13.20 (IO12); also elsewhere on the board
/Peripherie/BUZZER: U13.18 (IO10); also elsewhere on the board
GND: C24.2, C25.2, C26.2, SW1.1, SW2.1, U13.1 (GND), U13.40 (GND), U13.41 (GND); also elsewhere on the board

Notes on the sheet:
[0603]
ESP32-S3 chip strapping pins: GPIO 0. GPIO 3. GPIO 45. GPIO 46.

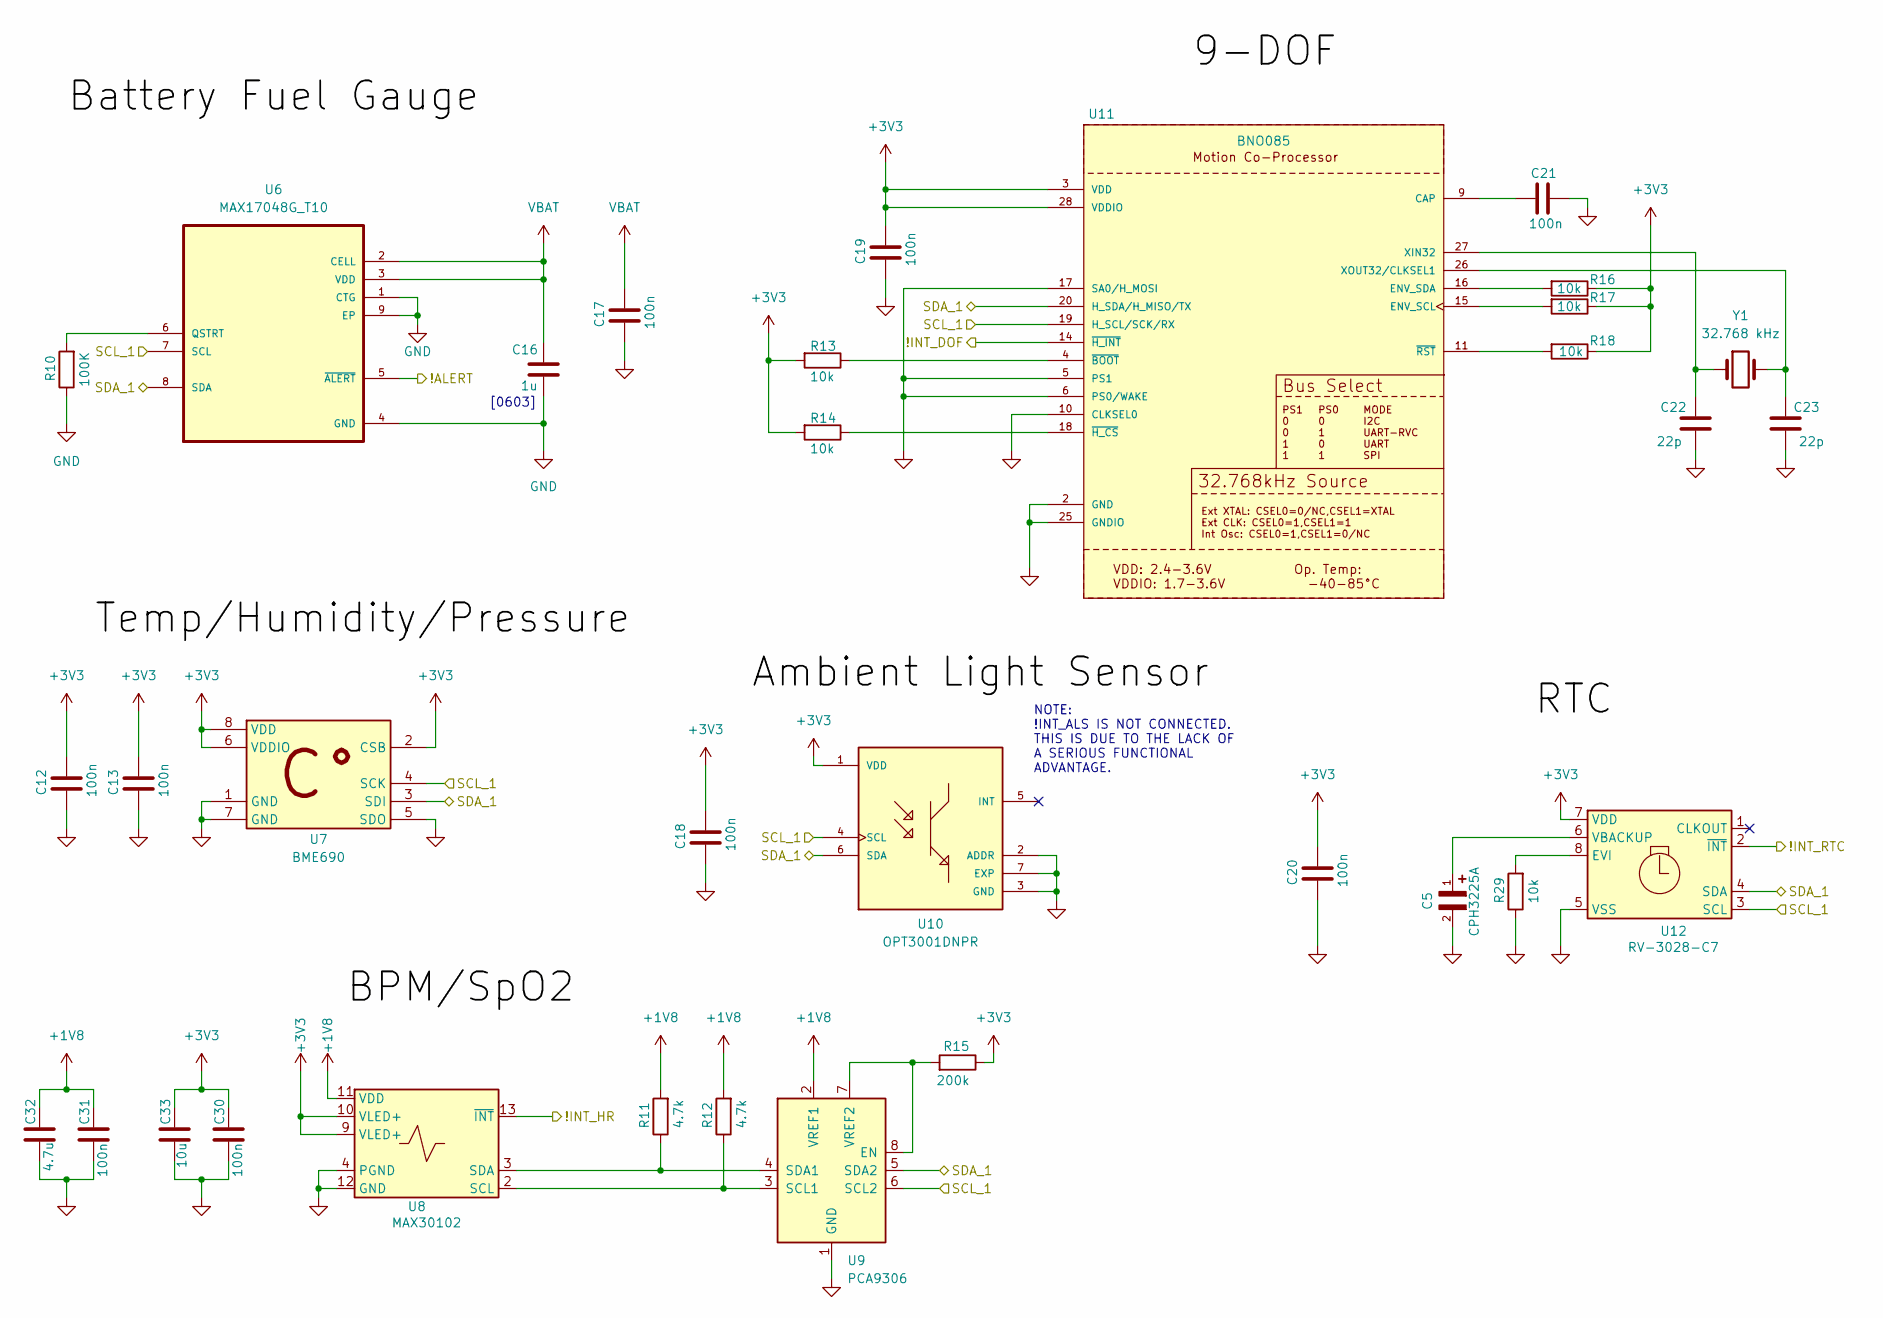
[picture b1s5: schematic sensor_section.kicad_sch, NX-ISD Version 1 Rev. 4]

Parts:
C5: CPH3225A; CAPCP3225X100N
C12, C13, C17, C18, C19, C20, C21, C30, C31: 100n; C_0402_1005Metric
C16: 1u; C_0603_1608Metric
C22, C23: 22p; C_0402_1005Metric
C32: 4.7u; C_0603_1608Metric
C33: 10u; C_0603_1608Metric
R10: 100K; R_0402_1005Metric
R11, R12: 4.7k; R_0402_1005Metric
R13, R14, R16, R17, R18, R29: 10k; R_0402_1005Metric
R15: 200k; R_0402_1005Metric
U6: MAX17048G_T10; SON50P200X200X80-9N
U7: BME690; Bosch_LGA-8_3x3mm_P0.8mm_ClockwisePinNumbering
U8: MAX30102; Maxim_OLGA-14_3.3x5.6mm_P0.8mm
U9: PCA9306; VSSOP-8_2.3x2mm_P0.5mm
U10: OPT3001DNPR; SON65P200X200X65-7N
U11: BNO085; IC_BNO085; PARTREV v1.17
U12: RV-3028-C7; MicroCrystal_C7_SON-8_1.5x3.2mm_P0.9mm
Y1: 32.768 kHz; Crystal_SMD_3215-2Pin_3.2x1.5mm; Tolerance ±20ppm; Manufacterer part number DH2032K768C5T1521011

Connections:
+1V8: C31.1, C32.1, R11.2, R12.2, U8.11 (VDD), U9.2 (VREF1); also elsewhere on the board
+3V3: C12.1, C13.1, C18.1, C19.1, C20.1, C30.1, C33.1, R13.2, R14.2, R15.1, R16.1, R17.1, R18.1, U7.2 (CSB), U7.6 (VDDIO), U7.8 (VDD), U8.9 (VLED+), U8.10 (VLED+), U10.1 (VDD), U11.3 (VDD), U11.28 (VDDIO), U12.7 (VDD); also elsewhere on the board
/Logic section/!ALERT: U6.5 (~ALERT); also elsewhere on the board
/Logic section/!INT_DOF: U11.14 (~H_INT); also elsewhere on the board
/Logic section/!INT_HR: U8.13 (~INT); also elsewhere on the board
/Logic section/!INT_RTC: U12.2 (~INT); also elsewhere on the board
/Logic section/SCL_1: U6.7 (SCL), U7.4 (SCK), U9.6 (SCL2), U10.4 (SCL), U11.19 (H_SCL/SCK/RX), U12.3 (SCL); also elsewhere on the board
/Logic section/SDA_1: U6.8 (SDA), U7.3 (SDI), U9.5 (SDA2), U10.6 (SDA), U11.20 (H_SDA/H_MISO/TX), U12.4 (SDA); also elsewhere on the board
GND: C5.2, C12.2, C13.2, C16.2, C17.2, C18.2, C19.2, C20.2, C21.1, C22.2, C23.2, C30.2, C31.2, C32.2, C33.2, R10.1, R29.1, U6.1 (CTG), U6.4 (GND), U6.9 (EP), U7.1 (GND), U7.5 (SDO), U7.7 (GND), U8.4 (PGND), U8.12 (GND), U9.1 (GND), U10.2 (ADDR), U10.3 (GND), U10.7 (EXP), U11.2 (GND), U11.5 (PS1), U11.6 (PS0/WAKE), U11.10 (CLKSEL0), U11.17 (SA0/H_MOSI), U11.25 (GNDIO), U12.5 (VSS); also elsewhere on the board
unnamed: R10.2, U6.6 (QSTRT)
unnamed: R12.1, U8.2 (SCL), U9.3 (SCL1)
unnamed: R11.1, U8.3 (SDA), U9.4 (SDA1)
unnamed: R15.2, U9.7 (VREF2), U9.8 (EN)
unnamed: C21.2, U11.9 (CAP)
unnamed: R17.2, U11.15 (ENV_SCL)
unnamed: R16.2, U11.16 (ENV_SDA)
unnamed: C22.1, U11.27 (XIN32), Y1.1
unnamed: C23.1, U11.26 (XOUT32/CLKSEL1), Y1.2
unnamed: R13.1, U11.4 (~BOOT)
unnamed: R14.1, U11.18 (~H_CS)
unnamed: R18.2, U11.11 (~RST)
unnamed: R29.2, U12.8 (EVI)
unnamed: C5.1, U12.6 (VBACKUP)
VBAT: C16.1, C17.1, U6.2 (CELL), U6.3 (VDD); also elsewhere on the board

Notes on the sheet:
[0603]
NOTE: !INT_ALS IS NOT CONNECTED. THIS IS DUE TO THE LACK OF A SERIOUS FUNCTIONAL ADVANTAGE.

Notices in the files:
ISD-PCB/README.md:
9. Hardware Licensing:
The hardware design files in this directory are licensed under the **CERN Open Hardware Licence Version 2 - Strongly Reciprocal (CERN-OHL-S)**. See the root `LICENSE` file for full terms and conditions.
